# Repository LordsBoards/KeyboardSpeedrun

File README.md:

# Speedrun 40% PCB Keyboard Design with KiCAD

**Keyboard design is supposed to be hard, isn't it? No longer.**

## Features

- ARM microcontroller with 256k of flash, USB, and QMK/Vial support
- USB-C port with ESD protection
- 4-layer board design
- 6 pin tag connect port for SWD programming
- Easy and quick routing

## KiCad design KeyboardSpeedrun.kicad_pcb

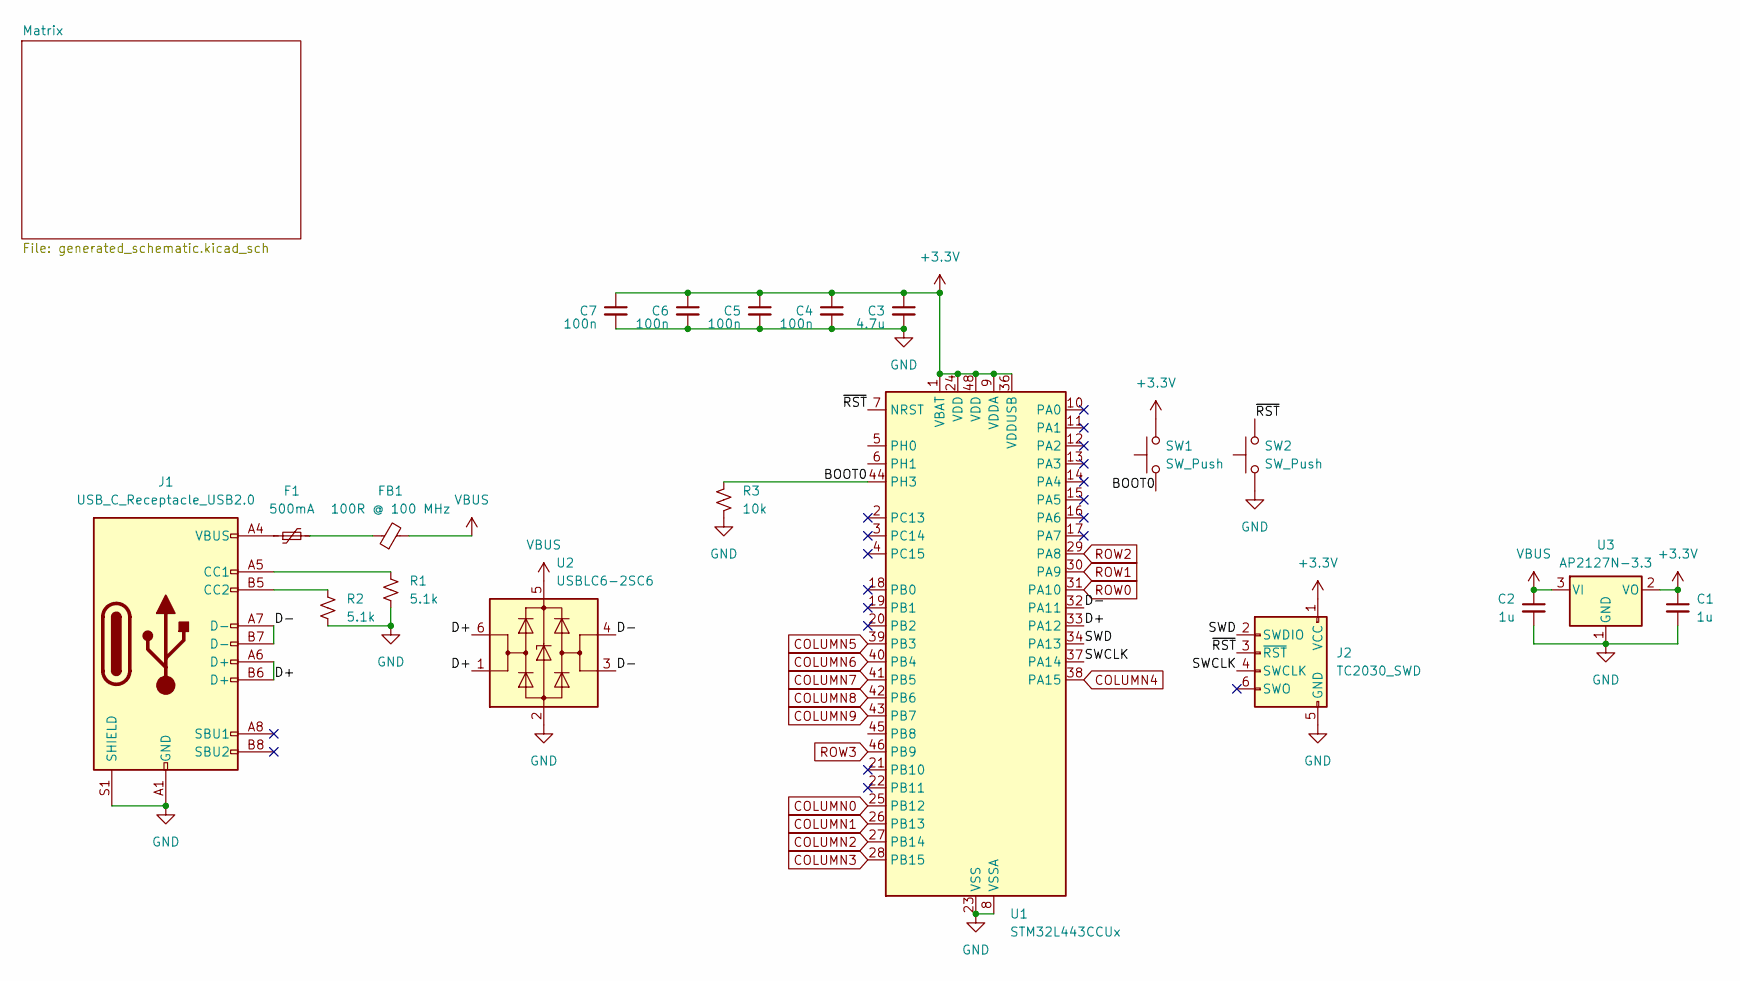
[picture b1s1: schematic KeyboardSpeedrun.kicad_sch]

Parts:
C1, C2: 1u; C_0402_1005Metric; LCSC C15684
C3: 4.7u; C_0402_1005Metric; LCSC C368809
C4, C5, C6, C7: 100n; C_0402_1005Metric; LCSC C169292
F1: 500mA; Fuse_0805_2012Metric; LCSC C2833485
FB1: 100R @ 100 MHz; L_0603_1608Metric; LCSC C14709
J1: USB_C_Receptacle_USB2.0; USB_C_Receptacle_HRO_TYPE-C-31-M-12; LCSC C165948
J2: TC2030_SWD; CON_TC2030_outlined
R1, R2: 5.1k; R_0402_1005Metric; LCSC C2906948
R3: 10k; R_0402_1005Metric; LCSC C60490
SW1, SW2: SW_Push; SW_SPST_SKQG_WithStem; LCSC C318884
U1: STM32L443CCUx; QFN-48-1EP_7x7mm_P0.5mm_EP5.6x5.6mm_ThermalVias; LCSC C1338637
U2: USBLC6-2SC6; SOT-23-6; LCSC C7519
U3: AP2127N-3.3; SOT-23; LCSC C347222

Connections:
+3.3V: C1.1, C3.1, C4.1, C5.1, C6.1, C7.1, J2.1 (VCC), SW1.2, U1.1 (VBAT), U1.9 (VDDA), U1.24 (VDD), U1.36 (VDDUSB), U1.48 (VDD), U3.2 (VO)
/BOOT0: R3.1, SW1.1, U1.44 (PH3)
/D+: J1.A6 (D+), J1.B6 (D+), U1.33 (PA12), U2.1 (I/O1), U2.6 (I/O1)
/D-: J1.A7 (D-), J1.B7 (D-), U1.32 (PA11), U2.3 (I/O2), U2.4 (I/O2)
/SWCLK: J2.4 (SWCLK), U1.37 (PA14)
/SWD: J2.2 (SWDIO), U1.34 (PA13)
/~RST: J2.3 (~RST), SW2.2, U1.7 (NRST)
COLUMN0: U1.25 (PB12); also elsewhere on the board
COLUMN1: U1.26 (PB13); also elsewhere on the board
COLUMN2: U1.27 (PB14); also elsewhere on the board
COLUMN3: U1.28 (PB15); also elsewhere on the board
COLUMN4: U1.38 (PA15); also elsewhere on the board
COLUMN5: U1.39 (PB3); also elsewhere on the board
COLUMN6: U1.40 (PB4); also elsewhere on the board
COLUMN7: U1.41 (PB5); also elsewhere on the board
COLUMN8: U1.42 (PB6); also elsewhere on the board
COLUMN9: U1.43 (PB7); also elsewhere on the board
GND: C1.2, C2.2, C3.2, C4.2, C5.2, C6.2, C7.2, J1.A1 (GND), J1.A12 (GND), J1.B1 (GND), J1.B12 (GND), J1.S1 (SHIELD), J2.5 (GND), R1.2, R2.2, R3.2, SW2.1, U1.8 (VSSA), U1.23 (VSS), U1.35 (VSS), U1.47 (VSS), U1.49 (VSS), U2.2 (GND), U3.1 (GND)
unnamed: F1.1, J1.A4 (VBUS), J1.A9 (VBUS), J1.B4 (VBUS), J1.B9 (VBUS)
unnamed: F1.2, FB1.1
unnamed: J1.A5 (CC1), R1.1
unnamed: J1.B5 (CC2), R2.1
ROW0: U1.31 (PA10); also elsewhere on the board
ROW1: U1.30 (PA9); also elsewhere on the board
ROW2: U1.29 (PA8); also elsewhere on the board
ROW3: U1.46 (PB9); also elsewhere on the board
VBUS: C2.1, FB1.2, U2.5 (VBUS), U3.3 (VI)

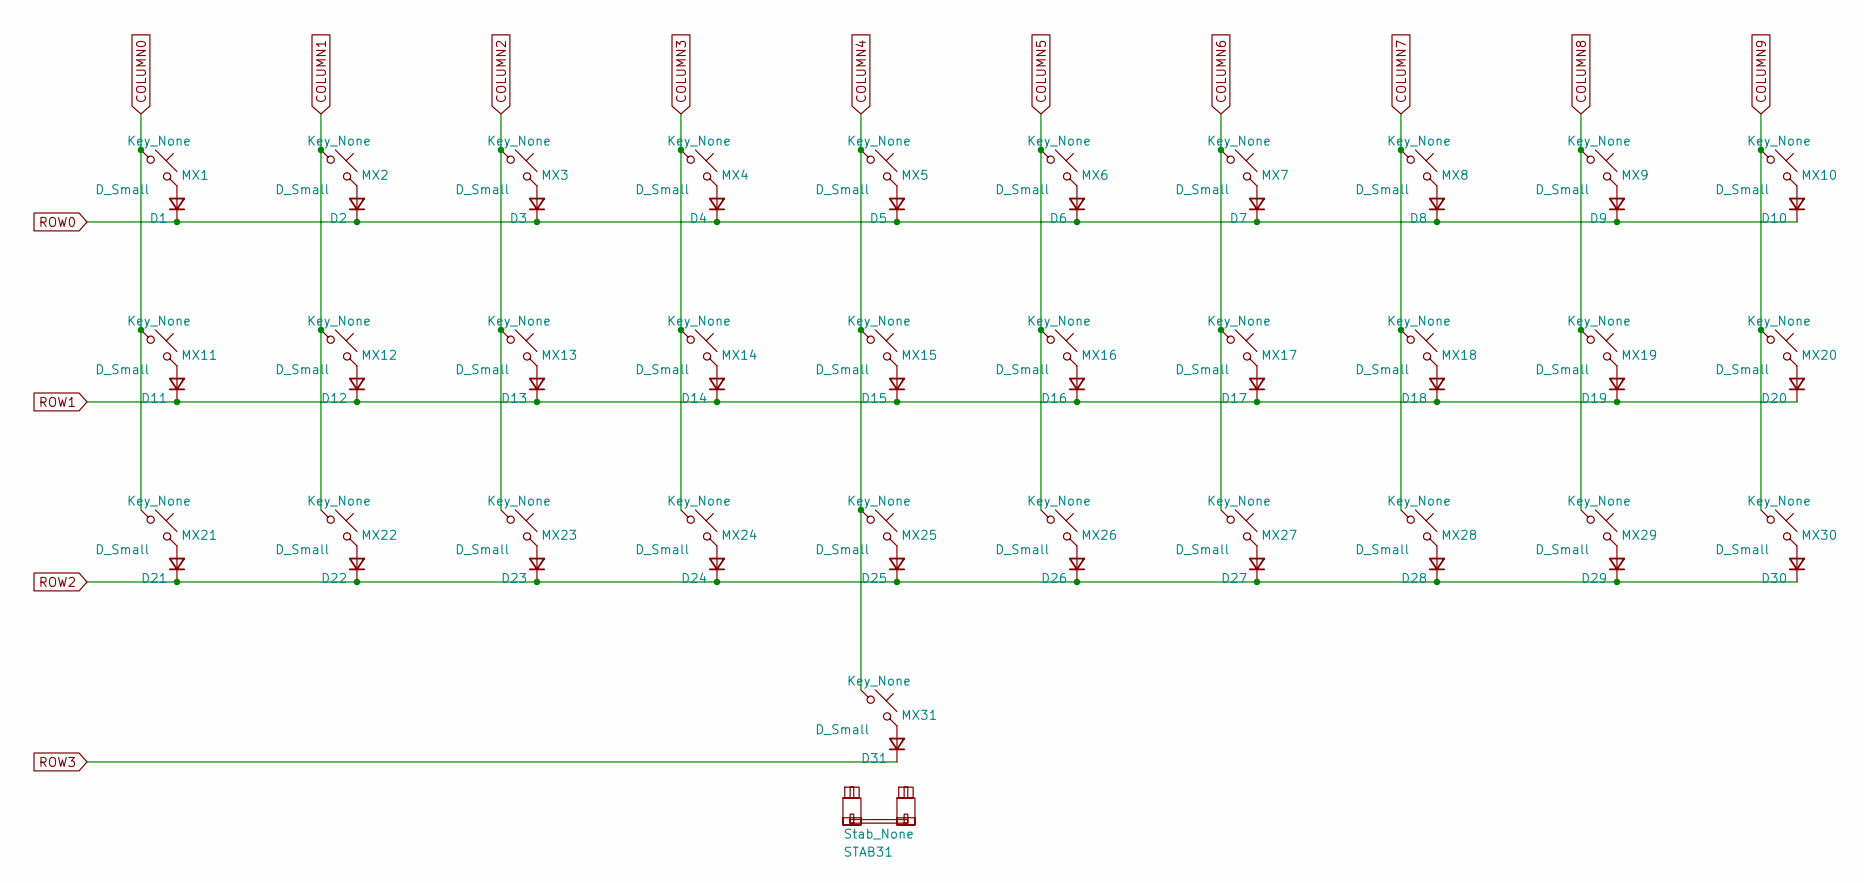
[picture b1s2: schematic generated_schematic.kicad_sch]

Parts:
D1, D2, D3, D4, D5, D6, D7, D8, D9, D10, D11, D12, D13, D14, D15, D16, D17, D18, D19, D20, D21, D22, D23, D24, D25, D26, D27, D28, D29, D30, D31: D_Small; D_SOD-123; LCSC C81598
MX1, MX2, MX3, MX4, MX5, MX6, MX7, MX8, MX9, MX10, MX11, MX12, MX13, MX14, MX15, MX16, MX17, MX18, MX19, MX20, MX21, MX22, MX23, MX24, MX25, MX26, MX27, MX28, MX29, MX30, MX31: Key_None; SW_MX_1u
STAB31: Stab_None; STAB_MX_P_10u

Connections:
COLUMN0: MX1.1, MX11.1, MX21.1; also elsewhere on the board
COLUMN1: MX2.1, MX12.1, MX22.1; also elsewhere on the board
COLUMN2: MX3.1, MX13.1, MX23.1; also elsewhere on the board
COLUMN3: MX4.1, MX14.1, MX24.1; also elsewhere on the board
COLUMN4: MX5.1, MX15.1, MX25.1, MX31.1; also elsewhere on the board
COLUMN5: MX6.1, MX16.1, MX26.1; also elsewhere on the board
COLUMN6: MX7.1, MX17.1, MX27.1; also elsewhere on the board
COLUMN7: MX8.1, MX18.1, MX28.1; also elsewhere on the board
COLUMN8: MX9.1, MX19.1, MX29.1; also elsewhere on the board
COLUMN9: MX10.1, MX20.1, MX30.1; also elsewhere on the board
unnamed: D1.2 (A), MX1.2
unnamed: D2.2 (A), MX2.2
unnamed: D3.2 (A), MX3.2
unnamed: D4.2 (A), MX4.2
unnamed: D5.2 (A), MX5.2
unnamed: D6.2 (A), MX6.2
unnamed: D7.2 (A), MX7.2
unnamed: D8.2 (A), MX8.2
unnamed: D9.2 (A), MX9.2
unnamed: D10.2 (A), MX10.2
unnamed: D11.2 (A), MX11.2
unnamed: D12.2 (A), MX12.2
unnamed: D13.2 (A), MX13.2
unnamed: D14.2 (A), MX14.2
unnamed: D15.2 (A), MX15.2
unnamed: D16.2 (A), MX16.2
unnamed: D17.2 (A), MX17.2
unnamed: D18.2 (A), MX18.2
unnamed: D19.2 (A), MX19.2
unnamed: D20.2 (A), MX20.2
unnamed: D21.2 (A), MX21.2
unnamed: D22.2 (A), MX22.2
unnamed: D23.2 (A), MX23.2
unnamed: D24.2 (A), MX24.2
unnamed: D25.2 (A), MX25.2
unnamed: D26.2 (A), MX26.2
unnamed: D27.2 (A), MX27.2
unnamed: D28.2 (A), MX28.2
unnamed: D29.2 (A), MX29.2
unnamed: D30.2 (A), MX30.2
unnamed: D31.2 (A), MX31.2
ROW0: D1.1 (K), D2.1 (K), D3.1 (K), D4.1 (K), D5.1 (K), D6.1 (K), D7.1 (K), D8.1 (K), D9.1 (K), D10.1 (K); also elsewhere on the board
ROW1: D11.1 (K), D12.1 (K), D13.1 (K), D14.1 (K), D15.1 (K), D16.1 (K), D17.1 (K), D18.1 (K), D19.1 (K), D20.1 (K); also elsewhere on the board
ROW2: D21.1 (K), D22.1 (K), D23.1 (K), D24.1 (K), D25.1 (K), D26.1 (K), D27.1 (K), D28.1 (K), D29.1 (K), D30.1 (K); also elsewhere on the board
ROW3: D31.1 (K); also elsewhere on the board

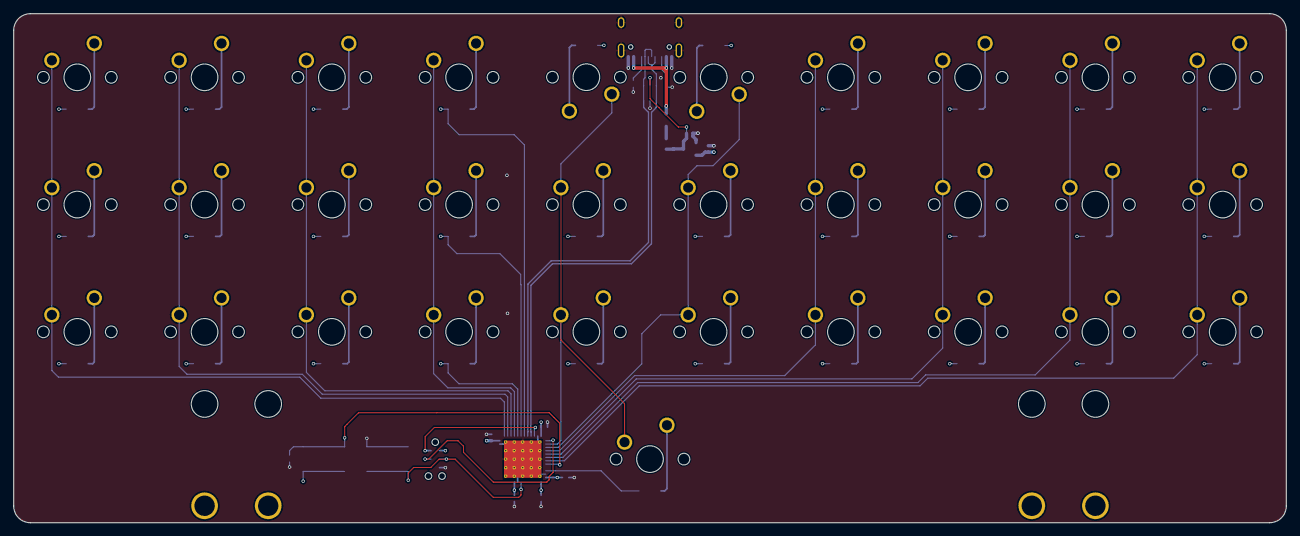
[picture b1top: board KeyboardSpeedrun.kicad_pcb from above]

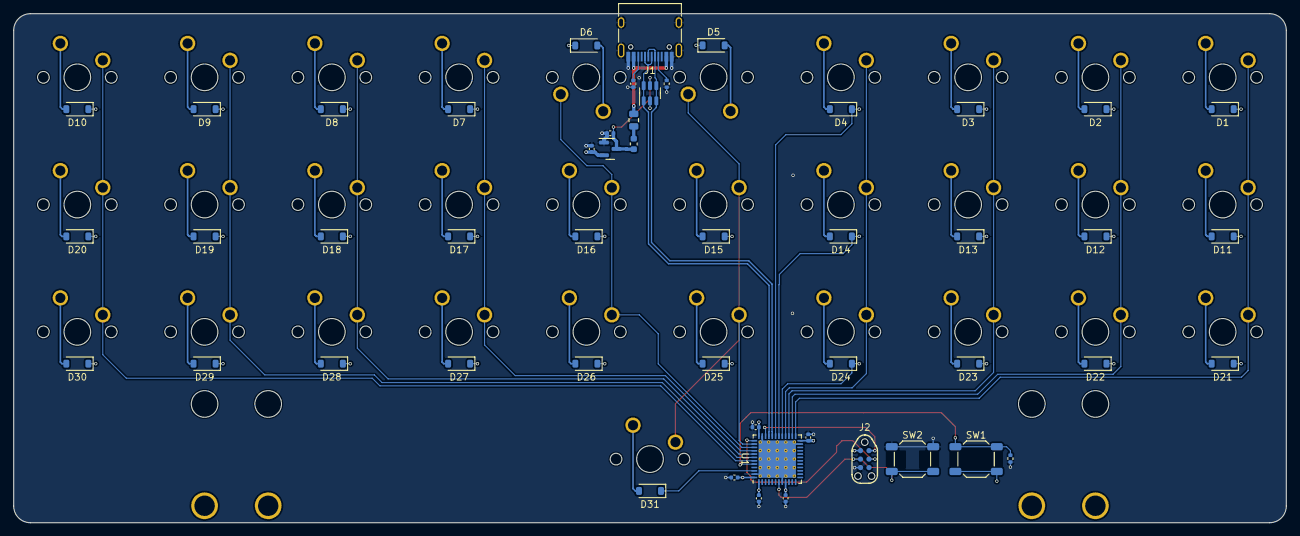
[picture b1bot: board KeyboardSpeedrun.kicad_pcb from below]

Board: 4 copper layers, 190.5 x 76.2 mm, 82 parts (50 on the bottom side), 58 nets.

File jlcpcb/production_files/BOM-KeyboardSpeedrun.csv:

Comment,Designator,Footprint,LCSC
STM32L443CCUx,U1,QFN-48-1EP_7x7mm_P0.5mm_EP5.6x5.6mm_ThermalVias,C1338637
100R @ 100 MHz,FB1,L_0603_1608Metric,C14709
1u,"C1,C2",C_0402_1005Metric,C15684
USB_C_Receptacle_USB2.0,J1,USB_C_Receptacle_HRO_TYPE-C-31-M-12,C165948
100n,"C4,C5,C6,C7",C_0402_1005Metric,C169292
500mA,F1,Fuse_0805_2012Metric,C2833485
5.1k,"R1,R2",R_0402_1005Metric,C2906948
SW_Push,"SW1,SW2",SW_SPST_SKQG_WithStem,C318884
AP2127N-3.3,U3,SOT-23,C347222
4.7u,C3,C_0402_1005Metric,C368809
10k,R3,R_0402_1005Metric,C60490
USBLC6-2SC6,U2,SOT-23-6,C7519
D_Small,"D1,D10,D11,D12,D13,D14,D15,D16,D17,D18,D19,D2,D20,D21,D22,D23,D24,D25,D26,D27,D28,D29,D3,D30,D31,D4,D5,D6,D7,D8,D9",D_SOD-123,C81598

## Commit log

2023-08-23 Initial commit.
2023-08-23 Changed readme extension
